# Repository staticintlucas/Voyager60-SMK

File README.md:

# Voyager60-SMK

A fully featured SMK-specific 60% PCB

This is a fork of [ai03's Voyager60-Alps](https://github.com/ai03-2725/Voyager60/tree/alps), adapted for [SMK 2nd generation](https://deskthority.net/wiki/SMK_second_generation) switches

## Note: this PCB is currently untested. As expressed in the LICENSE file, I am not liable if this design does not work

### Features

* RGB underglow
* Decent amount of layout compatibility - [View supported layouts](http://www.keyboard-layout-editor.com/#/gists/c867bdba7e5ae8be282f77a242bacf66)
* Slot cutout for maximum flexibility and typing comfort
* Over-current and static discharge protection
* Fully open-source

### Credits

This project is a fork of [ai03's Voyager60-Alps](https://github.com/ai03-2725/Voyager60/tree/alps)

This project borrows some of the compatible layouts from [Hasu's Alps64](https://github.com/tmk/alps64), especially regarding ISO compatibility positions.

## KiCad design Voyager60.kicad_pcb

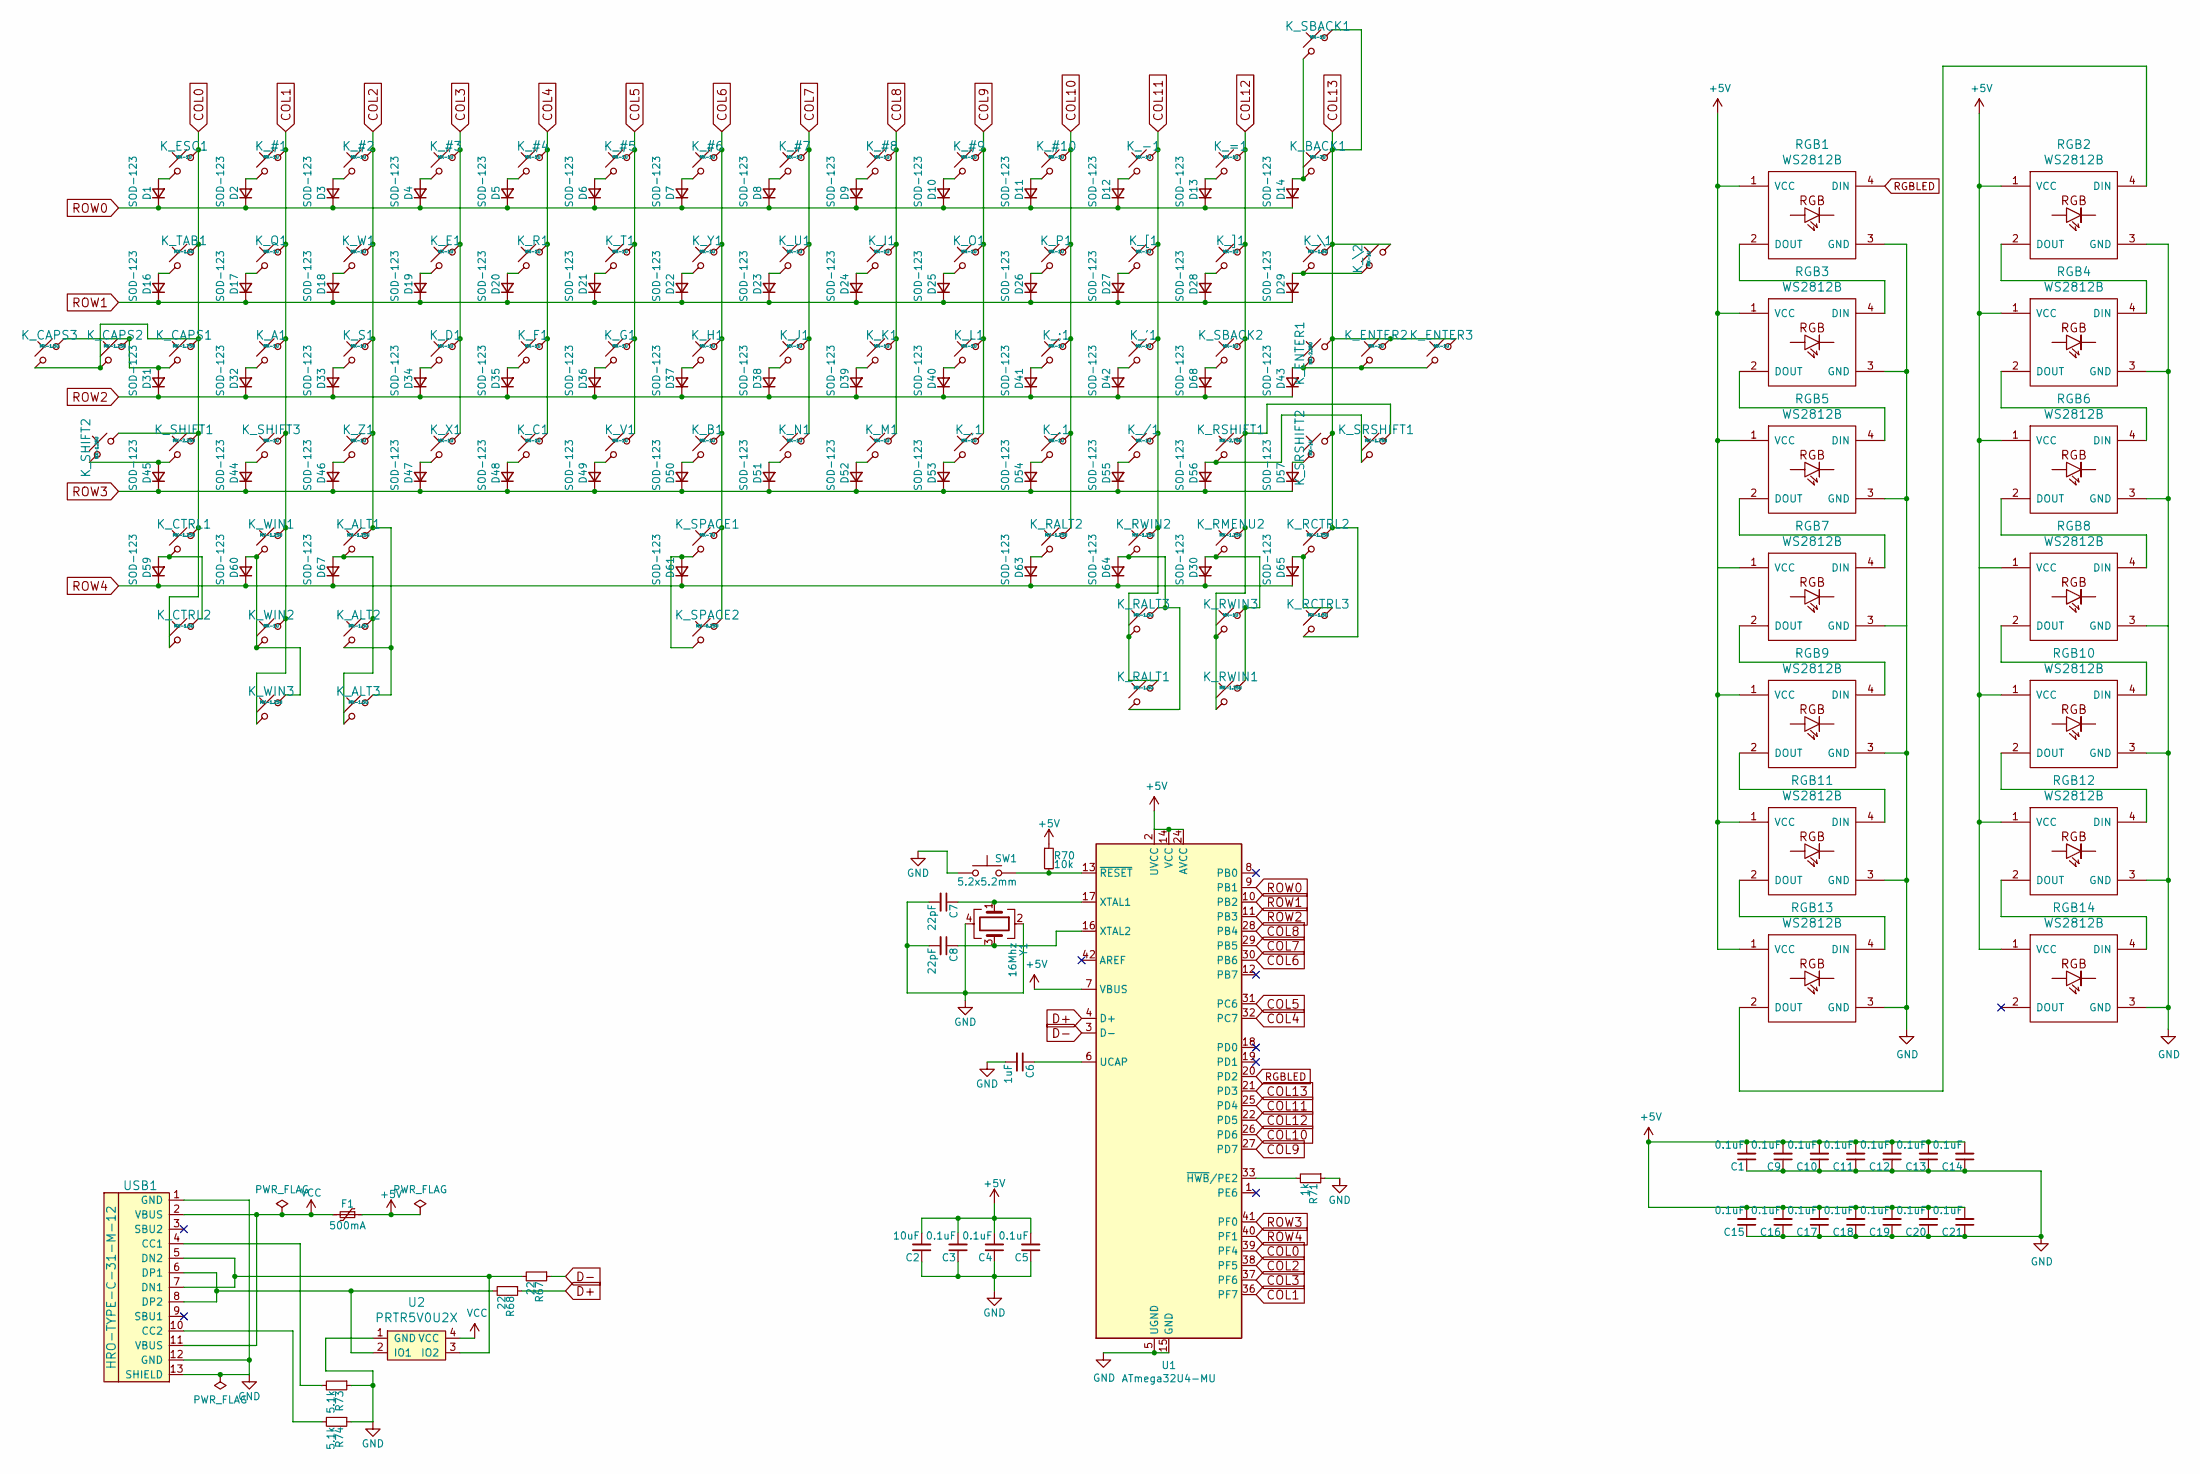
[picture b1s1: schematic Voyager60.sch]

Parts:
C1, C3, C4, C5, C9, C10, C11, C12, C13, C14, C15, C16, C17, C18, C19, C20, C21: 0.1uF; C_0603
C2: 10uF; C_0603
C6: 1uF; C_0603
C7, C8: 22pF; C_0603
D1, D2, D3, D4, D5, D6, D7, D8, D9, D10, D11, D12, D13, D14, D16, D17, D18, D19, D20, D21, D22, D23, D24, D25, D26, D27, D28, D29, D30, D31, D32, D33, D34, D35, D36, D37, D38, D39, D40, D41, D42, D43, D44, D45, D46, D47, D48, D49, D50, D51, D52, D53, D54, D55, D56, D57, D59, D60, D61, D63, D64, D65, D67, D68: SOD-123; D_SOD-123
F1: 500mA; Fuse_SMD1206_Reflow
K_#1, K_#2, K_#3, K_#4, K_#5, K_#6, K_#7, K_#8, K_#9, K_#10: MX-1U; SW_SMK
K_'1: MX-1U; SW_SMK
K_,1: MX-1U; SW_SMK
K_-1: MX-1U; SW_SMK
K_.1: MX-1U; SW_SMK
K_/1: MX-1U; SW_SMK
K_;1: MX-1U; SW_SMK
K_=1: MX-1U; SW_SMK
K_A1: MX-1U; SW_SMK
K_ALT1: MX-1.25U; SW_SMK
K_ALT2, K_ALT3: MX-1.5U; SW_SMK
K_B1: MX-1U; SW_SMK
K_BACK1: MX-2U; SW_SMK_2u
K_C1: MX-1U; SW_SMK
K_CAPS1: MX-1.75U; SW_SMK
K_CAPS2: MX-1.25U; SW_SMK
K_CAPS3: MX-1.5U; SW_SMK
K_CTRL1: MX-1.25U; SW_SMK
K_CTRL2: MX-1.5U; SW_SMK
K_D1: MX-1U; SW_SMK
K_E1: MX-1U; SW_SMK
K_ENTER1: MX-2.25U; SW_SMK_2u
K_ENTER2: MX-2U; SW_SMK_2u_R
K_ENTER3: MX-1U; SW_SMK
K_ESC1: MX-1U; SW_SMK
K_F1: MX-1U; SW_SMK
K_G1: MX-1U; SW_SMK
K_H1: MX-1U; SW_SMK
K_I1: MX-1U; SW_SMK
K_J1: MX-1U; SW_SMK
K_K1: MX-1U; SW_SMK
K_L1: MX-1U; SW_SMK
K_M1: MX-1U; SW_SMK
K_N1: MX-1U; SW_SMK
K_O1: MX-1U; SW_SMK
K_P1: MX-1U; SW_SMK
K_Q1: MX-1U; SW_SMK
K_R1: MX-1U; SW_SMK
K_RALT1, K_RALT3: MX-1.5U; SW_SMK
K_RALT2: MX-1.25U; SW_SMK
K_RCTRL2: MX-1.25U; SW_SMK
K_RCTRL3: MX-1.5U; SW_SMK
K_RMENU2: MX-1.25U; SW_SMK
K_RSHIFT1: MX-2.75U; SW_SMK_2u
K_RWIN1, K_RWIN2: MX-1.25U; SW_SMK
K_RWIN3: MX-1U; SW_SMK
K_S1: MX-1U; SW_SMK
K_SBACK1, K_SBACK2: MX-1U; SW_SMK
K_SHIFT1: MX-2.25U; SW_SMK_2u
K_SHIFT2: MX-1.25U; SW_SMK
K_SHIFT3: MX-1U; SW_SMK
K_SPACE1: MX-7U; SW_SMK_7u_R
K_SPACE2: MX-6.25U; SW_SMK_6.25u_R
K_SRSHIFT1: MX-1.75U; SW_SMK
K_SRSHIFT2: MX-1U; SW_SMK
K_T1: MX-1U; SW_SMK
K_TAB1: MX-1.5U; SW_SMK
K_U1: MX-1U; SW_SMK
K_V1: MX-1U; SW_SMK
K_W1: MX-1U; SW_SMK
K_WIN1, K_WIN3: MX-1.25U; SW_SMK
K_WIN2: MX-1U; SW_SMK
K_X1: MX-1U; SW_SMK
K_Y1: MX-1U; SW_SMK
K_Z1: MX-1U; SW_SMK
K_[1: MX-1U; SW_SMK
K_\1: MX-1.5U; SW_SMK
K_\2: MX-1U; SW_SMK
K_]1: MX-1U; SW_SMK
R67, R68: 22; R_0805
R70: 10k; R_0805
R71: 1k; R_0805
R73, R74: 5.1k; R_0805
RGB1, RGB2, RGB3, RGB4, RGB5, RGB6, RGB7, RGB8, RGB9, RGB10, RGB11, RGB12, RGB13, RGB14: WS2812B
SW1: 5.2x5.2mm; SW_SPST_SKQG_WithStem
U1: ATmega32U4-MU; QFN-44-1EP_7x7mm_P0.5mm_EP5.2x5.2mm
U2: PRTR5V0U2X; SOT143B
USB1: HRO-TYPE-C-31-M-12; HRO-TYPE-C-31-M-12-Assembly
Y1: 16Mhz; Crystal_SMD_3225-4pin_3.2x2.5mm

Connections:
+5V: C1.2, C2.2, C3.2, C4.2, C5.2, C9.2, C10.2, C11.2, C12.2, C13.2, C14.2, C15.2, C16.2, C17.2, C18.2, C19.2, C20.2, C21.2, F1.1, R70.1, RGB1.1 (VCC), RGB2.1 (VCC), RGB3.1 (VCC), RGB4.1 (VCC), RGB5.1 (VCC), RGB6.1 (VCC), RGB7.1 (VCC), RGB8.1 (VCC), RGB9.1 (VCC), RGB10.1 (VCC), RGB11.1 (VCC), RGB12.1 (VCC), RGB13.1 (VCC), RGB14.1 (VCC), U1.2 (UVCC), U1.7 (VBUS), U1.14 (VCC), U1.24 (AVCC), U1.34 (VCC), U1.44 (AVCC)
COL0: K_CAPS1.1, K_CAPS2.2, K_CAPS3.2, K_CTRL1.1, K_CTRL2.2, K_ESC1.1, K_SHIFT1.1, K_SHIFT2.2, K_TAB1.1, U1.39 (PF4)
COL1: K_#1.1, K_A1.1, K_Q1.1, K_SHIFT3.1, K_WIN1.1, K_WIN2.1, K_WIN3.2, U1.36 (PF7)
COL2: K_#2.1, K_ALT1.1, K_ALT2.2, K_ALT3.1, K_S1.1, K_W1.1, K_Z1.1, U1.38 (PF5)
COL3: K_#3.1, K_D1.1, K_E1.1, K_X1.1, U1.37 (PF6)
COL4: K_#4.1, K_C1.1, K_F1.1, K_R1.1, U1.32 (PC7)
COL5: K_#5.1, K_G1.1, K_T1.1, K_V1.1, U1.31 (PC6)
COL6: K_#6.1, K_B1.1, K_H1.1, K_SPACE1.1, K_SPACE2.1, K_Y1.1, U1.30 (PB6)
COL7: K_#7.1, K_J1.1, K_N1.1, K_U1.1, U1.29 (PB5)
COL8: K_#8.1, K_I1.1, K_K1.1, K_M1.1, U1.28 (PB4)
COL9: K_#9.1, K_,1.1, K_L1.1, K_O1.1, U1.27 (PD7)
COL10: K_#10.1, K_.1.1, K_;1.1, K_P1.1, K_RALT2.1, U1.26 (PD6)
COL11: K_'1.1, K_-1.1, K_/1.1, K_RALT1.1, K_RALT3.2, K_RWIN2.1, K_[1.1, U1.25 (PD4)
COL12: K_=1.1, K_RMENU2.1, K_RSHIFT1.1, K_RWIN1.2, K_RWIN3.2, K_SBACK2.1, K_SRSHIFT1.1, K_]1.1, U1.22 (PD5)
COL13: K_BACK1.1, K_ENTER1.2, K_ENTER2.1, K_ENTER3.1, K_RCTRL2.1, K_RCTRL3.2, K_SBACK1.1, K_SRSHIFT2.2, K_\1.1, K_\2.2, U1.21 (PD3)
D+: R68.1, U1.4 (D+)
D-: R67.1, U1.3 (D-)
GND: C1.1, C2.1, C3.1, C4.1, C5.1, C6.2, C7.2, C8.2, C9.1, C10.1, C11.1, C12.1, C13.1, C14.1, C15.1, C16.1, C17.1, C18.1, C19.1, C20.1, C21.1, R71.1, R73.1, R74.1, RGB1.3 (GND), RGB2.3 (GND), RGB3.3 (GND), RGB4.3 (GND), RGB5.3 (GND), RGB6.3 (GND), RGB7.3 (GND), RGB8.3 (GND), RGB9.3 (GND), RGB10.3 (GND), RGB11.3 (GND), RGB12.3 (GND), RGB13.3 (GND), RGB14.3 (GND), SW1.1, U1.5 (UGND), U1.15 (GND), U1.23 (GND), U1.35 (GND), U1.43 (GND), U1.45 (GND), U2.1 (GND), USB1.1 (GND), USB1.12 (GND), USB1.13 (SHIELD), Y1.2, Y1.4
unnamed: C6.1, U1.6 (UCAP)
unnamed: C7.1, U1.17 (XTAL1), Y1.1
unnamed: C8.1, U1.16 (XTAL2), Y1.3
unnamed: D1.2 (A), K_ESC1.2
unnamed: D2.2 (A), K_#1.2
unnamed: D3.2 (A), K_#2.2
unnamed: D4.2 (A), K_#3.2
unnamed: D5.2 (A), K_#4.2
unnamed: D6.2 (A), K_#5.2
unnamed: D7.2 (A), K_#6.2
unnamed: D8.2 (A), K_#7.2
unnamed: D9.2 (A), K_#8.2
unnamed: D10.2 (A), K_#9.2
unnamed: D11.2 (A), K_#10.2
unnamed: D12.2 (A), K_-1.2
unnamed: D13.2 (A), K_=1.2
unnamed: D14.2 (A), K_BACK1.2, K_SBACK1.2
unnamed: D16.2 (A), K_TAB1.2
unnamed: D17.2 (A), K_Q1.2
unnamed: D18.2 (A), K_W1.2
unnamed: D19.2 (A), K_E1.2
unnamed: D20.2 (A), K_R1.2
unnamed: D21.2 (A), K_T1.2
unnamed: D22.2 (A), K_Y1.2
unnamed: D23.2 (A), K_U1.2
unnamed: D24.2 (A), K_I1.2
unnamed: D25.2 (A), K_O1.2
unnamed: D26.2 (A), K_P1.2
unnamed: D27.2 (A), K_[1.2
unnamed: D28.2 (A), K_]1.2
unnamed: D29.2 (A), K_\1.2, K_\2.1
unnamed: D30.2 (A), K_RMENU2.2, K_RWIN1.1, K_RWIN3.1
unnamed: D31.2 (A), K_CAPS1.2, K_CAPS2.1, K_CAPS3.1
unnamed: D32.2 (A), K_A1.2
unnamed: D33.2 (A), K_S1.2
unnamed: D34.2 (A), K_D1.2
unnamed: D35.2 (A), K_F1.2
unnamed: D36.2 (A), K_G1.2
unnamed: D37.2 (A), K_H1.2
unnamed: D38.2 (A), K_J1.2
unnamed: D39.2 (A), K_K1.2
unnamed: D40.2 (A), K_L1.2
unnamed: D41.2 (A), K_;1.2
unnamed: D42.2 (A), K_'1.2
unnamed: D43.2 (A), K_ENTER1.1, K_ENTER2.2, K_ENTER3.2
unnamed: D44.2 (A), K_SHIFT3.2
unnamed: D45.2 (A), K_SHIFT1.2, K_SHIFT2.1
unnamed: D46.2 (A), K_Z1.2
unnamed: D47.2 (A), K_X1.2
unnamed: D48.2 (A), K_C1.2
unnamed: D49.2 (A), K_V1.2
unnamed: D50.2 (A), K_B1.2
unnamed: D51.2 (A), K_N1.2
unnamed: D52.2 (A), K_M1.2
unnamed: D53.2 (A), K_,1.2
unnamed: D54.2 (A), K_.1.2
unnamed: D55.2 (A), K_/1.2
unnamed: D56.2 (A), K_RSHIFT1.2, K_SRSHIFT1.2
unnamed: D57.2 (A), K_SRSHIFT2.1
unnamed: D59.2 (A), K_CTRL1.2, K_CTRL2.1
unnamed: D60.2 (A), K_WIN1.2, K_WIN2.2, K_WIN3.1
unnamed: D61.2 (A), K_SPACE1.2, K_SPACE2.2
unnamed: D63.2 (A), K_RALT2.2
unnamed: D64.2 (A), K_RALT1.2, K_RALT3.1, K_RWIN2.2
unnamed: D65.2 (A), K_RCTRL2.2, K_RCTRL3.1
unnamed: D67.2 (A), K_ALT1.2, K_ALT2.1, K_ALT3.2
unnamed: D68.2 (A), K_SBACK2.2
unnamed: R67.2, U2.3 (IO2), USB1.5 (DN2), USB1.7 (DN1)
unnamed: R68.2, U2.2 (IO1), USB1.6 (DP1), USB1.8 (DP2)
unnamed: R70.2, SW1.2, U1.13 (~RESET)
unnamed: R71.2, U1.33 (~HWB~/PE2)
unnamed: R73.2, USB1.4 (CC1)
unnamed: R74.2, USB1.10 (CC2)
unnamed: RGB1.2 (DOUT), RGB3.4 (DIN)
unnamed: RGB2.2 (DOUT), RGB4.4 (DIN)
unnamed: RGB3.2 (DOUT), RGB5.4 (DIN)
unnamed: RGB4.2 (DOUT), RGB6.4 (DIN)
unnamed: RGB5.2 (DOUT), RGB7.4 (DIN)
unnamed: RGB6.2 (DOUT), RGB8.4 (DIN)
unnamed: RGB7.2 (DOUT), RGB9.4 (DIN)
unnamed: RGB10.2 (DOUT), RGB12.4 (DIN)
unnamed: RGB8.2 (DOUT), RGB10.4 (DIN)
unnamed: RGB11.2 (DOUT), RGB13.4 (DIN)
unnamed: RGB9.2 (DOUT), RGB11.4 (DIN)
unnamed: RGB12.2 (DOUT), RGB14.4 (DIN)
unnamed: RGB2.4 (DIN), RGB13.2 (DOUT)
RGBLED: RGB1.4 (DIN), U1.20 (PD2)
ROW0: D1.1 (K), D2.1 (K), D3.1 (K), D4.1 (K), D5.1 (K), D6.1 (K), D7.1 (K), D8.1 (K), D9.1 (K), D10.1 (K), D11.1 (K), D12.1 (K), D13.1 (K), D14.1 (K), U1.9 (PB1)
ROW1: D16.1 (K), D17.1 (K), D18.1 (K), D19.1 (K), D20.1 (K), D21.1 (K), D22.1 (K), D23.1 (K), D24.1 (K), D25.1 (K), D26.1 (K), D27.1 (K), D28.1 (K), D29.1 (K), U1.10 (PB2)
ROW2: D31.1 (K), D32.1 (K), D33.1 (K), D34.1 (K), D35.1 (K), D36.1 (K), D37.1 (K), D38.1 (K), D39.1 (K), D40.1 (K), D41.1 (K), D42.1 (K), D43.1 (K), D68.1 (K), U1.11 (PB3)
ROW3: D44.1 (K), D45.1 (K), D46.1 (K), D47.1 (K), D48.1 (K), D49.1 (K), D50.1 (K), D51.1 (K), D52.1 (K), D53.1 (K), D54.1 (K), D55.1 (K), D56.1 (K), D57.1 (K), U1.41 (PF0)
ROW4: D30.1 (K), D59.1 (K), D60.1 (K), D61.1 (K), D63.1 (K), D64.1 (K), D65.1 (K), D67.1 (K), U1.40 (PF1)
VCC: F1.2, U2.4 (VCC), USB1.2 (VBUS), USB1.11 (VBUS)

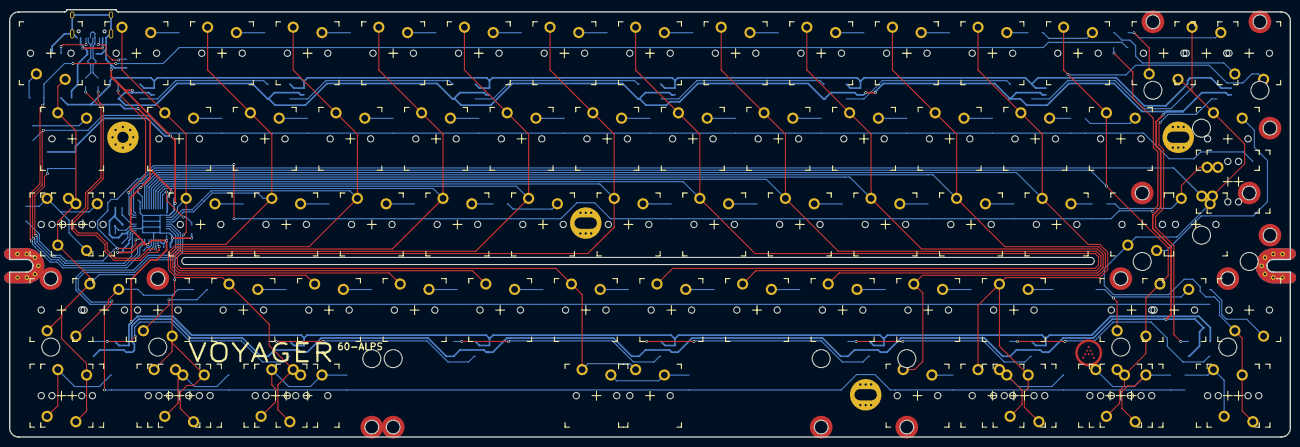
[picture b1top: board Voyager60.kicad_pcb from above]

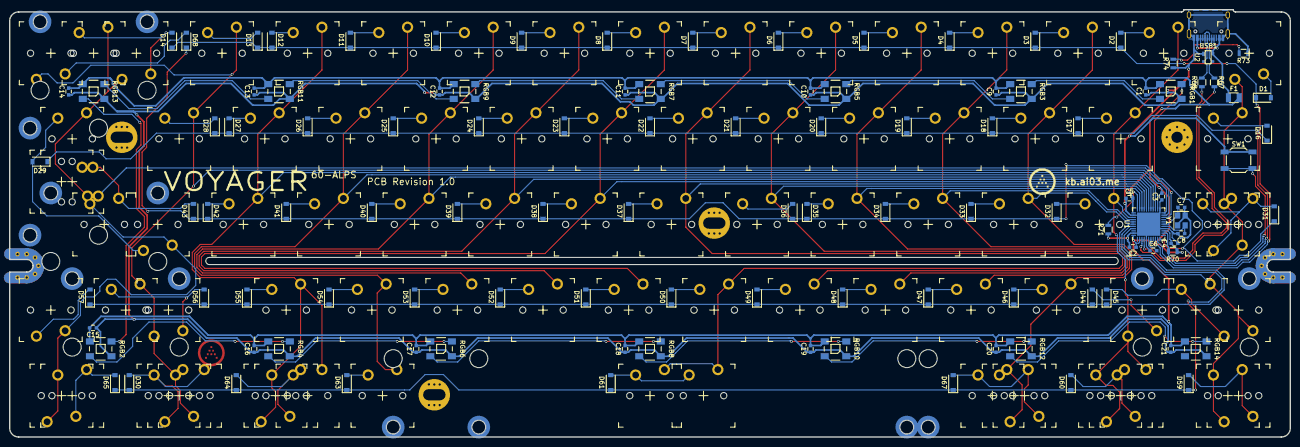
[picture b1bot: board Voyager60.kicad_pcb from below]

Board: 2 copper layers, 285.0 x 95.1 mm, 194 parts (111 on the bottom side), 111 nets.

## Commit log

2020-11-16 Remove unused files
2020-11-16 Add standard KiCad gitignore, remove another unused submodule
2020-11-16 Clean up rescued symbols in the schematic; get rid or all ERC errors/warnings
2020-11-26 Redo layout with SMK footprints
2020-11-30 Update README to reflect changes
2020-11-30 Update README, hopefully for the last time today
